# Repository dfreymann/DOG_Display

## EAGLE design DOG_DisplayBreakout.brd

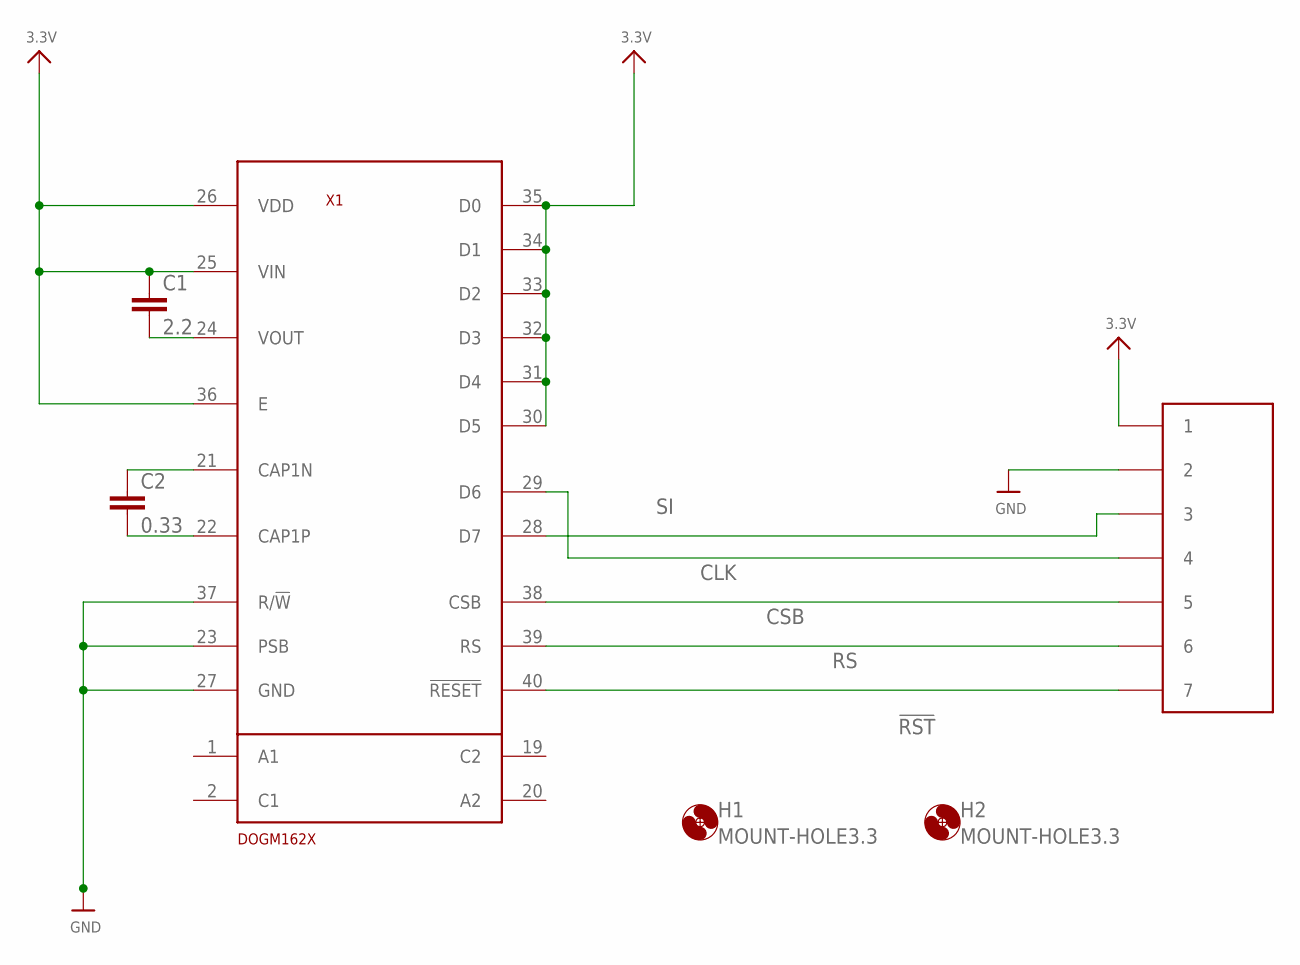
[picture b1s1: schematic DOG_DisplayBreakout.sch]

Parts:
C1: 2.2; 0805_BIGGERPAD-OK
C2: 0.33; 0805_BIGGERPAD-OK
CN1: JST_S7B-PH-K-S
H1, H2: MOUNT-HOLE3.3; HOLE3,3
X1: DOGM162X

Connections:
3.3V: C1.1, CN1.P1 (1), X1.25 (VIN), X1.26 (VDD), X1.30 (D5), X1.31 (D4), X1.32 (D3), X1.33 (D2), X1.34 (D1), X1.35 (D0), X1.36 (E)
!RST: CN1.P7 (7), X1.40 (!RESET)
CLK: CN1.P4 (4), X1.29 (D6)
CSB: CN1.P5 (5), X1.38 (CSB)
GND: CN1.P2 (2), X1.23 (PSB), X1.27 (GND), X1.37 (R/!W)
unnamed: C1.2, X1.24 (VOUT)
unnamed: C2.1, X1.21 (CAP1N)
unnamed: C2.2, X1.22 (CAP1P)
RS: CN1.P6 (6), X1.39 (RS)
SI: CN1.P3 (3), X1.28 (D7)

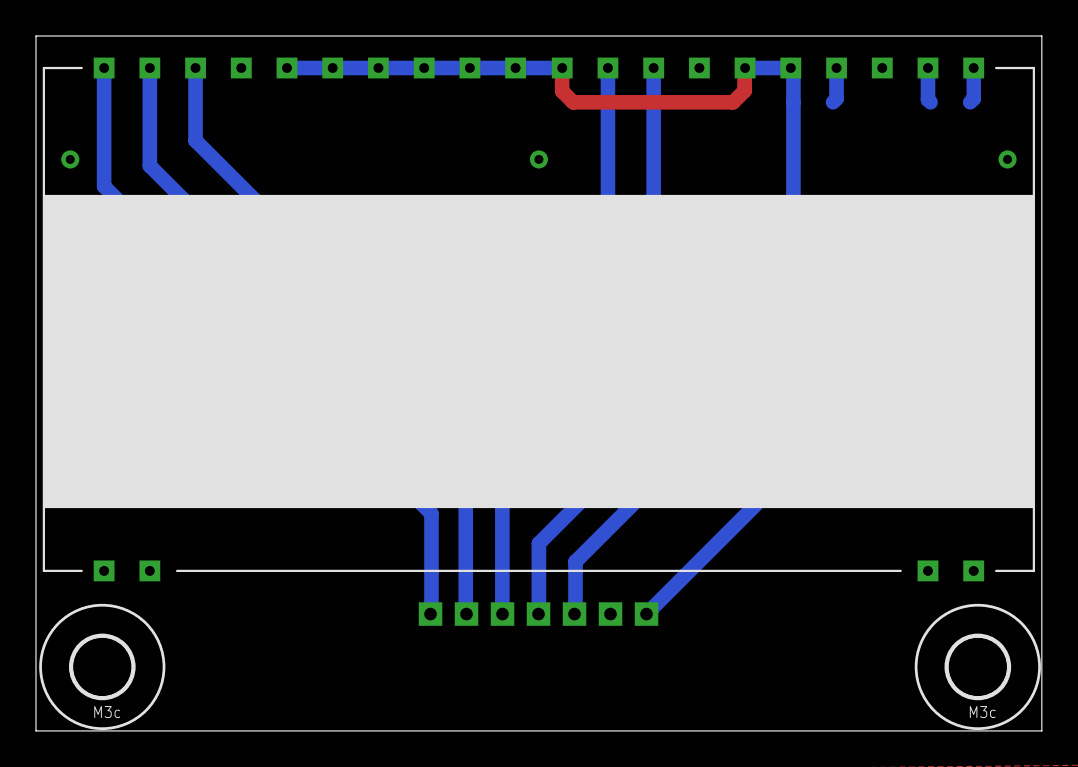
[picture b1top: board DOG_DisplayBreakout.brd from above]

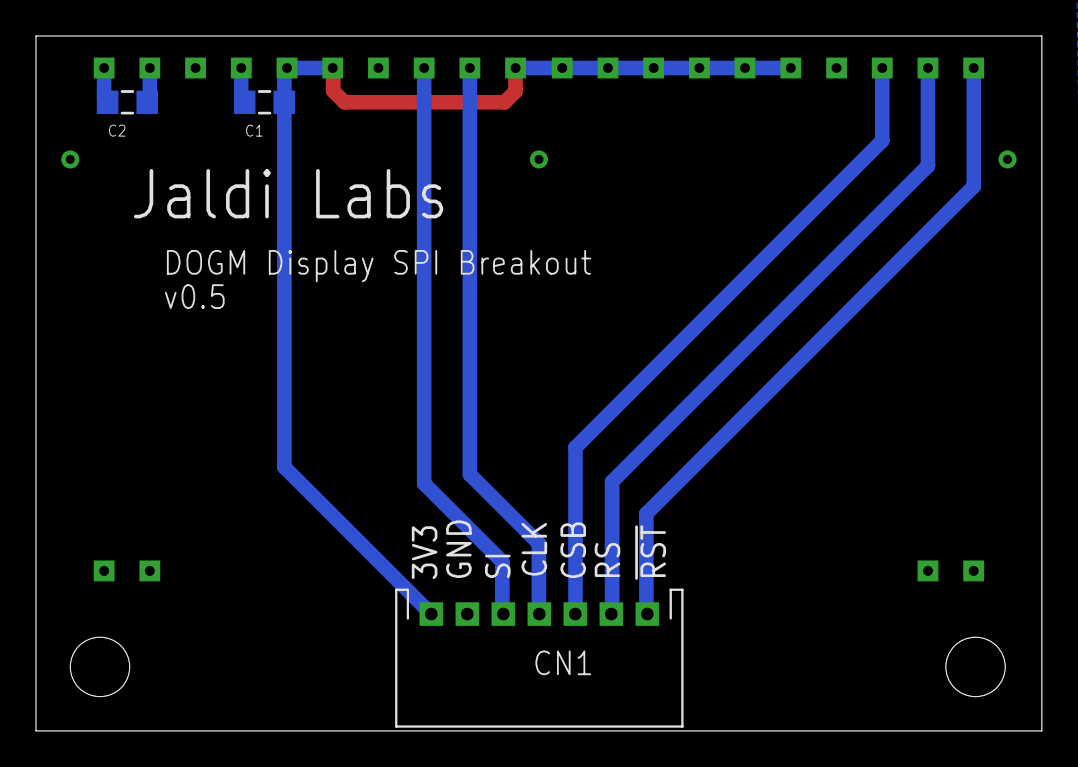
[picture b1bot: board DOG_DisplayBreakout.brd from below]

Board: 2 copper layers, 55.9 x 38.6 mm, 6 parts (3 on the bottom side), 10 nets.

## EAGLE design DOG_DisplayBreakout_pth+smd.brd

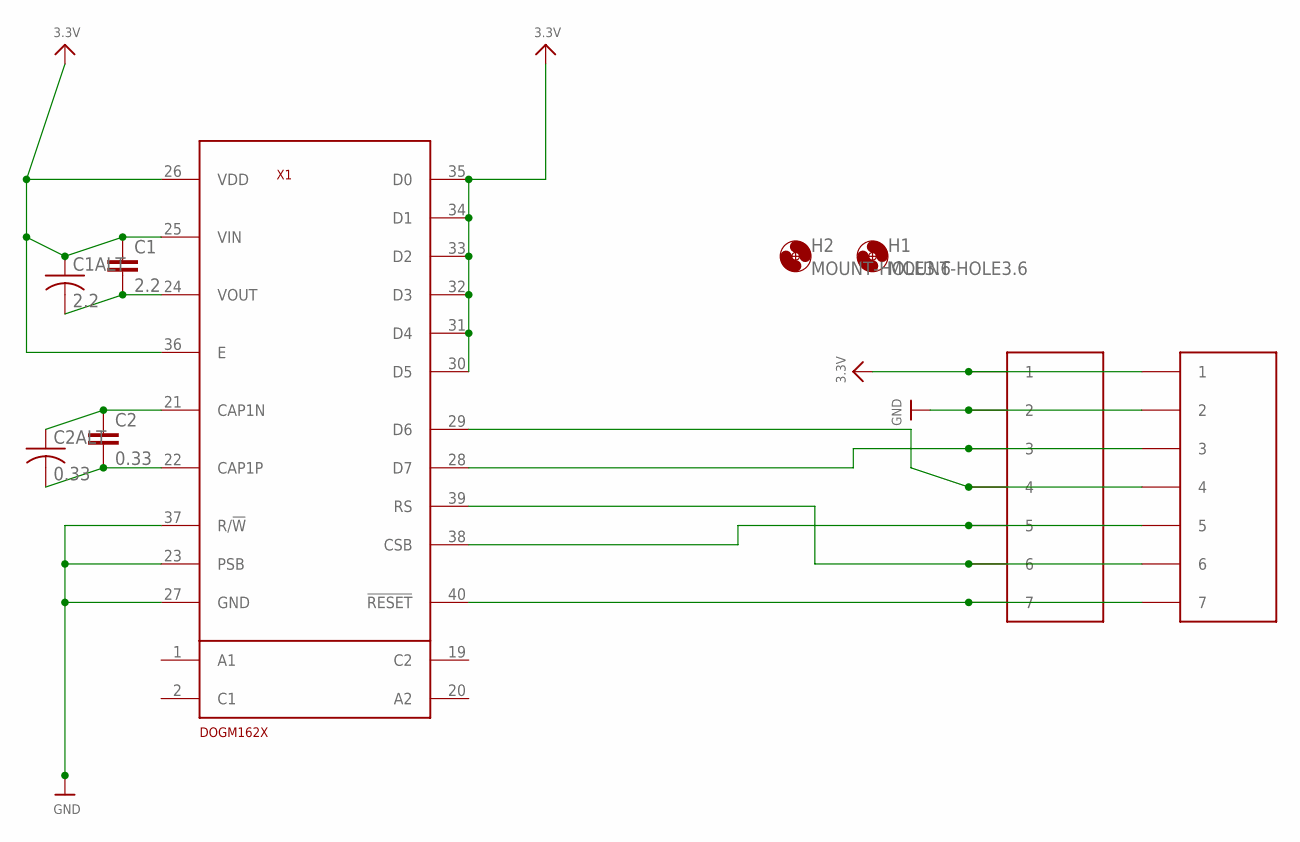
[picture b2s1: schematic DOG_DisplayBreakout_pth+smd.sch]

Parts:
C1: 2.2; 0805_BIGGERPAD-OK
C1ALT: 2.2; C050-035X075
C2: 0.33; 0805_BIGGERPAD-OK
C2ALT: 0.33; C050-024X044
CN1: JST_S7B-PH-SM4-TB
CN1ALT: JST_S7B-PH-K-S
H1, H2: MOUNT-HOLE3.6; HOLE3,6
X1: DOGM162X

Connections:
3.3V: C1.1, C1ALT.1, CN1.P$1 (1), CN1ALT.P1 (1), X1.25 (VIN), X1.26 (VDD), X1.30 (D5), X1.31 (D4), X1.32 (D3), X1.33 (D2), X1.34 (D1), X1.35 (D0), X1.36 (E)
CLK: CN1.P$4 (4), CN1ALT.P4 (4), X1.29 (D6)
CSB: CN1.P$5 (5), CN1ALT.P5 (5), X1.38 (CSB)
GND: CN1.P$2 (2), CN1ALT.P2 (2), X1.23 (PSB), X1.27 (GND), X1.37 (R/!W)
unnamed: C1.2, C1ALT.2, X1.24 (VOUT)
unnamed: C2.1, C2ALT.1, X1.21 (CAP1N)
unnamed: C2.2, C2ALT.2, X1.22 (CAP1P)
unnamed: CN1.P$7 (7), CN1ALT.P7 (7), X1.40 (!RESET)
unnamed: CN1.P$3 (3), CN1ALT.P3 (3), X1.28 (D7)
RS: CN1.P$6 (6), CN1ALT.P6 (6), X1.39 (RS)

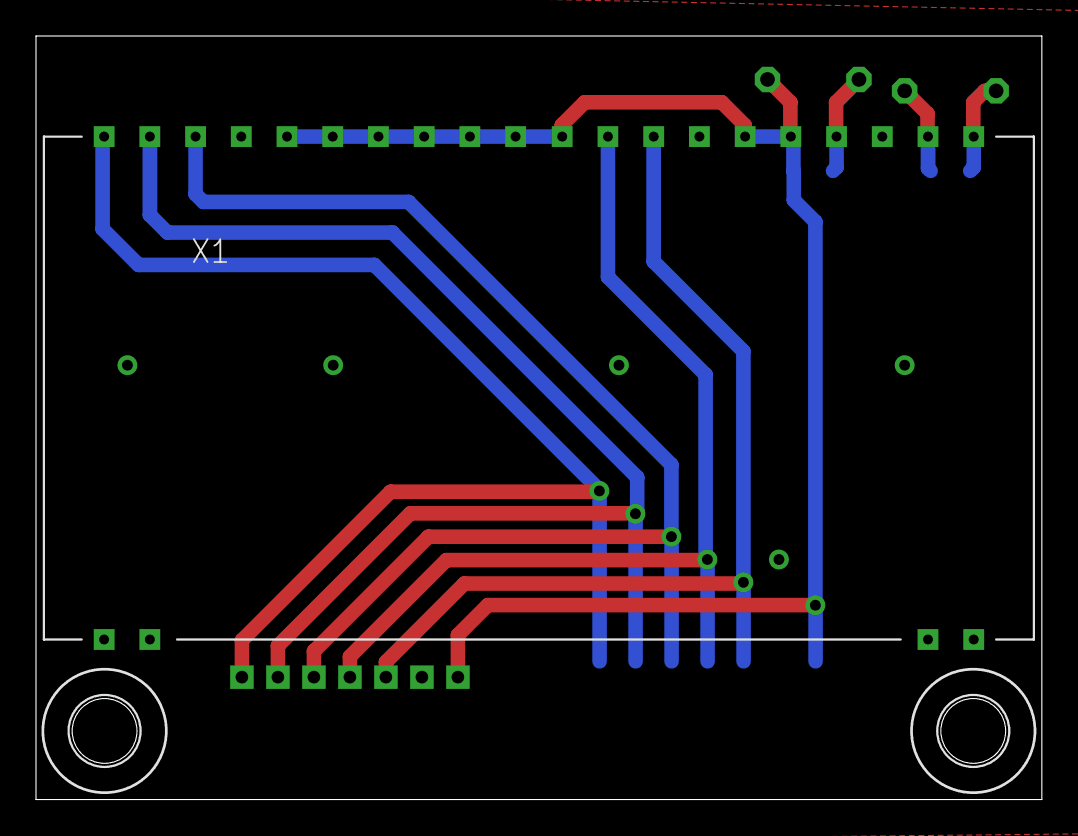
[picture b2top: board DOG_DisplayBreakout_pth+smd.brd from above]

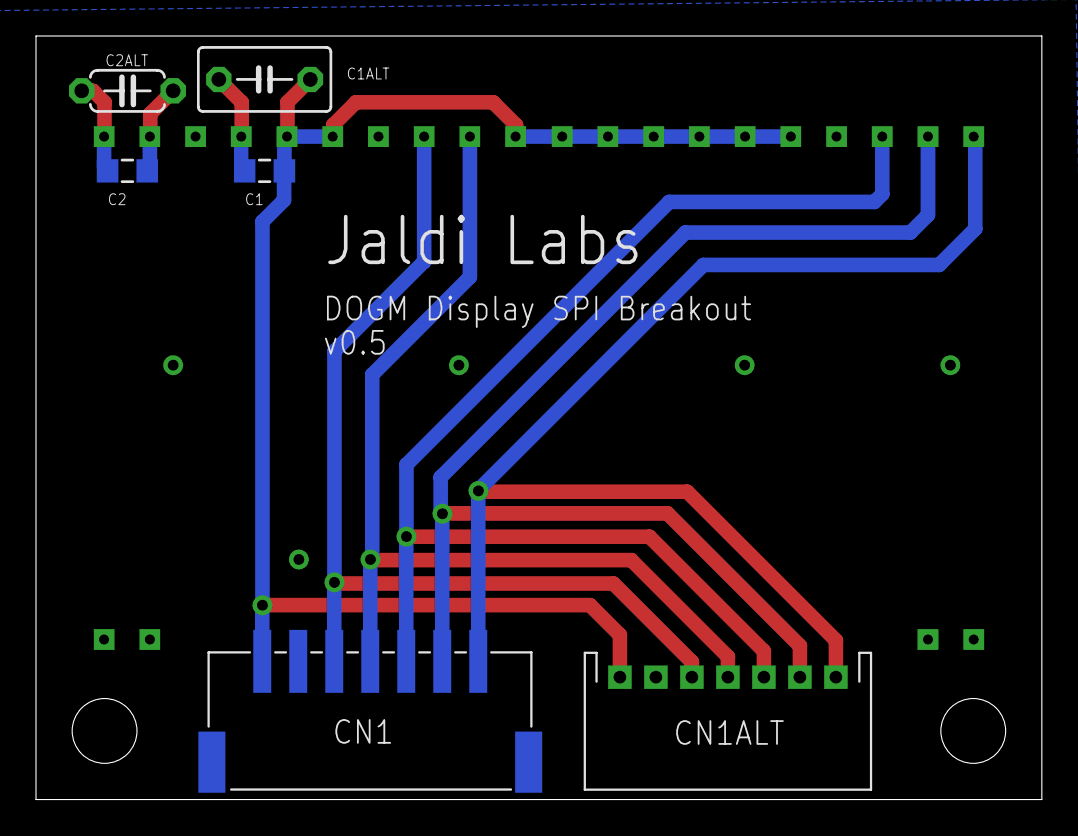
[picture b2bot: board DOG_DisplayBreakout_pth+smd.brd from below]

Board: 2 copper layers, 55.9 x 42.4 mm, 9 parts (6 on the bottom side), 10 nets.

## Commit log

2020-04-15 more comprehensive gitignore

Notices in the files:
parts and their libraries:
microbuilder: This work is placed in the public domain, and may be freely used for commercial and non-commercial work with the following conditions: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
